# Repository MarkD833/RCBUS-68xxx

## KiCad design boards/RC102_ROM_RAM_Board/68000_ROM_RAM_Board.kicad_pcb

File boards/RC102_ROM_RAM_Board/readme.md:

# ROM & RAM board - V1 - 128K ROM + 1M RAM

# Details
The ROM & RAM board is designed to plug into an RCBus-80 backplane with support for 128K ROM (via 2x Winbond W27C512 EEPROMs) and 1M RAM (via 2x Alliance Memory AS6C4008 SRAMs). The EEPROMs and SRAMs are used as a pair to allow 16-bit wide memory accesses.

## Address Decoding
The address decoding is carried out by a 74LS138 and divides the lower 8Mb of memory space into eight 1Mb blocks. The EEPROMs are hard wired to /CS0 (pin 15) and the SRAMs are hard wired to /CS1 (pin 14). This configuration always places the EEPROMs starting at address 0x000000 and the SRAMs starting at address 0x100000.

## Bus Width 
A 74LS139 generates the read and write signals for each of the memory chips and takes care of byte or word accesses.

## DTACK
A 74LS125 is used to generate a simple /DTACK signal driven directly from the EEPROM and SRAM chip select signals without any wait period.

# Board Assembly
Assembly of the board should be fairly straightforward as there are no surface mount devices to deal with.

When fitting the 80-pin right angle connector, initially only solder a couple of pins at opposite ends of the connector so that you can make any adjustments if the board is not vertical when fitted to the backplane.

# Winbond W27C512 EEPROMs
Be careful where you source these devices from. I bought mine from AliExpress and they were sold as new. In fact they were salvaged from boards and the IC legs were tinned with solder. This makes the pins slightly "sticky" when you insert the chips into IC sockets. My experience with these chips is that you may get 6-10 insertions/removals before the IC socket spring contacts start to break.

# Errors
None so far.

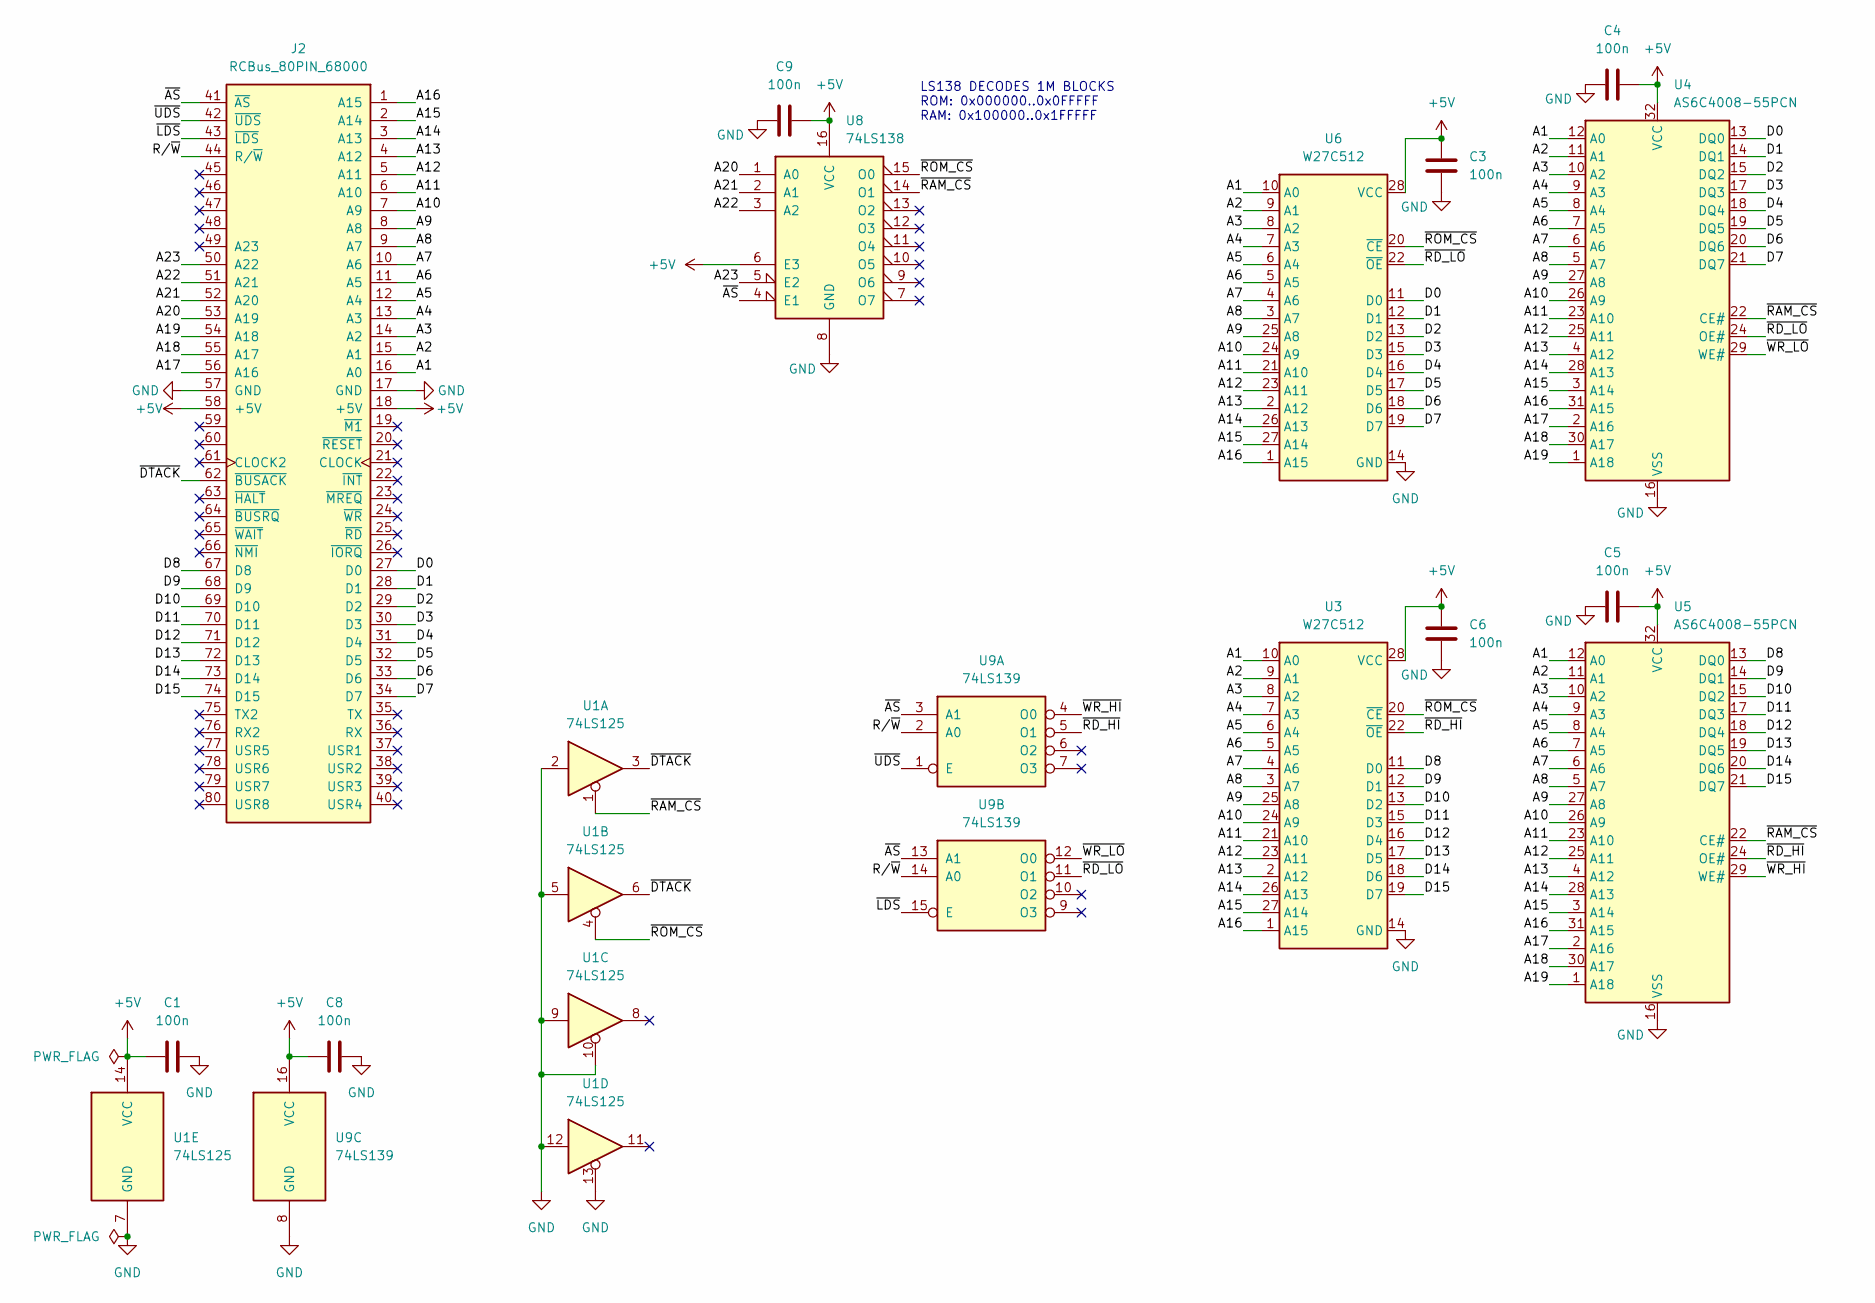
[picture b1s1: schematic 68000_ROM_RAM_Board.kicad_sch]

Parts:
C1, C3, C4, C5, C6, C8, C9: 100n; C_Disc_D5.0mm_W2.5mm_P2.50mm
J2: RCBus_80PIN_68000; RCBus_80p_Medium
U1: 74LS125; DIP-14_W7.62mm
U3, U6: W27C512; DIP-28_W15.24mm
U4, U5: AS6C4008-55PCN; DIP-32_W15.24mm
U8: 74LS138; DIP-16_W7.62mm
U9: 74LS139; DIP-16_W7.62mm

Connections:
+5V: C1.1, C3.1, C4.2, C5.2, C6.1, C8.1, C9.2, J2.18 (+5V), J2.58 (+5V), U1.14 (VCC), U3.28 (VCC), U4.32 (VCC), U5.32 (VCC), U6.28 (VCC), U8.6 (E3), U8.16 (VCC), U9.16 (VCC)
/A1: J2.16 (A0), U3.10 (A0), U4.12 (A0), U5.12 (A0), U6.10 (A0)
/A2: J2.15 (A1), U3.9 (A1), U4.11 (A1), U5.11 (A1), U6.9 (A1)
/A3: J2.14 (A2), U3.8 (A2), U4.10 (A2), U5.10 (A2), U6.8 (A2)
/A4: J2.13 (A3), U3.7 (A3), U4.9 (A3), U5.9 (A3), U6.7 (A3)
/A5: J2.12 (A4), U3.6 (A4), U4.8 (A4), U5.8 (A4), U6.6 (A4)
/A6: J2.11 (A5), U3.5 (A5), U4.7 (A5), U5.7 (A5), U6.5 (A5)
/A7: J2.10 (A6), U3.4 (A6), U4.6 (A6), U5.6 (A6), U6.4 (A6)
/A8: J2.9 (A7), U3.3 (A7), U4.5 (A7), U5.5 (A7), U6.3 (A7)
/A9: J2.8 (A8), U3.25 (A8), U4.27 (A8), U5.27 (A8), U6.25 (A8)
/A10: J2.7 (A9), U3.24 (A9), U4.26 (A9), U5.26 (A9), U6.24 (A9)
/A11: J2.6 (A10), U3.21 (A10), U4.23 (A10), U5.23 (A10), U6.21 (A10)
/A12: J2.5 (A11), U3.23 (A11), U4.25 (A11), U5.25 (A11), U6.23 (A11)
/A13: J2.4 (A12), U3.2 (A12), U4.4 (A12), U5.4 (A12), U6.2 (A12)
/A14: J2.3 (A13), U3.26 (A13), U4.28 (A13), U5.28 (A13), U6.26 (A13)
/A15: J2.2 (A14), U3.27 (A14), U4.3 (A14), U5.3 (A14), U6.27 (A14)
/A16: J2.1 (A15), U3.1 (A15), U4.31 (A15), U5.31 (A15), U6.1 (A15)
/A17: J2.56 (A16), U4.2 (A16), U5.2 (A16)
/A18: J2.55 (A17), U4.30 (A17), U5.30 (A17)
/A19: J2.54 (A18), U4.1 (A18), U5.1 (A18)
/A20: J2.53 (A19), U8.1 (A0)
/A21: J2.52 (A20), U8.2 (A1)
/A22: J2.51 (A21), U8.3 (A2)
/A23: J2.50 (A22), U8.5 (E2)
/D0: J2.27 (D0), U4.13 (DQ0), U6.11 (D0)
/D1: J2.28 (D1), U4.14 (DQ1), U6.12 (D1)
/D2: J2.29 (D2), U4.15 (DQ2), U6.13 (D2)
/D3: J2.30 (D3), U4.17 (DQ3), U6.15 (D3)
/D4: J2.31 (D4), U4.18 (DQ4), U6.16 (D4)
/D5: J2.32 (D5), U4.19 (DQ5), U6.17 (D5)
/D6: J2.33 (D6), U4.20 (DQ6), U6.18 (D6)
/D7: J2.34 (D7), U4.21 (DQ7), U6.19 (D7)
/D8: J2.67 (D8), U3.11 (D0), U5.13 (DQ0)
/D9: J2.68 (D9), U3.12 (D1), U5.14 (DQ1)
/D10: J2.69 (D10), U3.13 (D2), U5.15 (DQ2)
/D11: J2.70 (D11), U3.15 (D3), U5.17 (DQ3)
/D12: J2.71 (D12), U3.16 (D4), U5.18 (DQ4)
/D13: J2.72 (D13), U3.17 (D5), U5.19 (DQ5)
/D14: J2.73 (D14), U3.18 (D6), U5.20 (DQ6)
/D15: J2.74 (D15), U3.19 (D7), U5.21 (DQ7)
/R/~W: J2.44 (R/~W), U9.2 (A0), U9.14 (A0)
/~AS: J2.41 (~AS), U8.4 (E1), U9.3 (A1), U9.13 (A1)
/~DTACK: J2.62 (~BUSACK), U1.3, U1.6
/~LDS: J2.43 (~LDS), U9.15 (E)
/~RAM_CS: U1.1, U4.22 (CE#), U5.22 (CE#), U8.14 (O1)
/~RD_HI: U3.22 (~OE), U5.24 (OE#), U9.5 (O1)
/~RD_LO: U4.24 (OE#), U6.22 (~OE), U9.11 (O1)
/~ROM_CS: U1.4, U3.20 (~CE), U6.20 (~CE), U8.15 (O0)
/~UDS: J2.42 (~UDS), U9.1 (E)
/~WR_HI: U5.29 (WE#), U9.4 (O0)
/~WR_LO: U4.29 (WE#), U9.12 (O0)
GND: C1.2, C3.2, C4.1, C5.1, C6.2, C8.2, C9.1, J2.17 (GND), J2.57 (GND), U1.2, U1.5, U1.7 (GND), U1.9, U1.10, U1.12, U1.13, U3.14 (GND), U4.16 (VSS), U5.16 (VSS), U6.14 (GND), U8.8 (GND), U9.8 (GND)

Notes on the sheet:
LS138 DECODES 1M BLOCKS ROM: 0x000000..0x0FFFFF RAM: 0x100000..0x1FFFFF

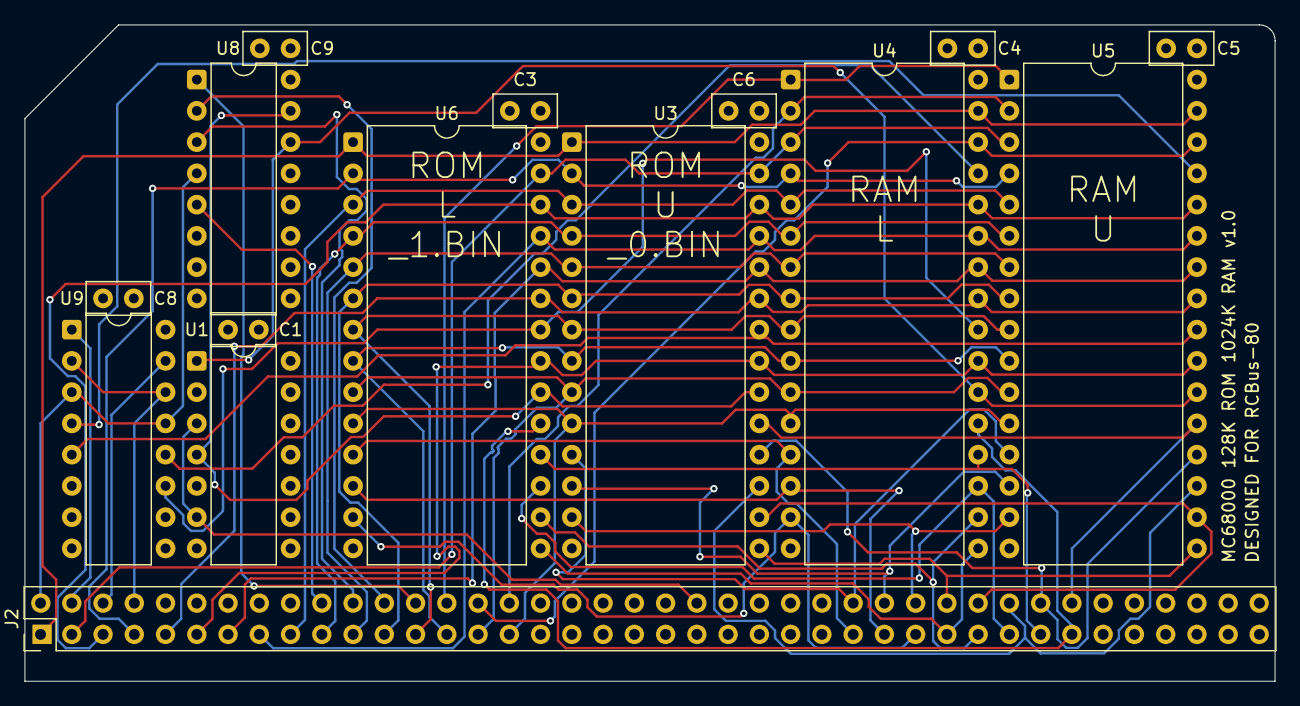
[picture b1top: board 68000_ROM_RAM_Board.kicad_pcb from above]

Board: 4 copper layers, 101.6 x 53.3 mm, 15 parts (0 on the bottom side), 52 nets.

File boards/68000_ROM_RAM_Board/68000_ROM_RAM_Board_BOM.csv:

"Reference","Value","Datasheet","Footprint","Qty","Description"
"C1,C3,C4,C5,C6,C8,C9","100n","~","Capacitor_THT:C_Disc_D5.0mm_W2.5mm_P2.50mm","7","Unpolarized ceramic capacitor"
"J2","RCBus_80PIN_68000","~","MyLibrary2023:RCBus_80p_Medium","1","Generic 02x40 pin connector, right angle"
"U1","74LS125","http://www.ti.com/lit/gpn/sn74LS125","Package_DIP:DIP-14_W7.62mm","1","Quad buffer 3-State outputs"
"U3,U6","W27C512","","Package_DIP:DIP-28_W15.24mm","2","EEPROM 64K x 8 DIP28"
"U4,U5","AS6C4008-55PCN","https://www.alliancememory.com/wp-content/uploads/pdf/AS6C4008.pdf","Package_DIP:DIP-32_W15.24mm","2","512K x 8 Low Power CMOS RAM, DIP-32"
"U8","74LS138","http://www.ti.com/lit/gpn/sn74LS138","Package_DIP:DIP-16_W7.62mm","1","Decoder 3 to 8 active low outputs"
"U9","74LS139","http://www.ti.com/lit/ds/symlink/sn74ls139a.pdf","Package_DIP:DIP-16_W7.62mm","1","Dual Decoder 1 of 4, Active low outputs"

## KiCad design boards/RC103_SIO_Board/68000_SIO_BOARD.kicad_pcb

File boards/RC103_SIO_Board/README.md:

# Quad Serial I/O Board

# Details
The serial board is populated with two 68681 (or equivalent) DUARTS giving 4 UARTs in total. The 4 serial ports are each fed to a 6-pin connector at the board edge. The layout of the 6 pins is compatible with an FTDI USB-TTL Serial interface board. Both DUART chips do not have to be fitted. The board will work with just one chip fitted.

## Address Decoding
The address decoding is carried out by a 74LS688 combined with a 74LS138 to generate 8 separate 2048 byte blocks residing between addresses $D00000 and $D03FFF.

The base address of each DUART is determined by the placement of a jumper between adjacent pins on J1 & J9 (DUART A) and J1 & J11 (DUART B).

## Device Register Access
The registers of the 68681 DUART are 8 bits wide and are accessed on consecutive ODD addresses from the base address set by the address decode logic. Assuming that the /CS0 jumper has been fitted for DUART #1, then the first few registers are accessed on the following addresses:
+ $D00001 : Mode Register A (R/W)
+ $D00003 : Status Register A (R) / Clock Select Register A (W)
+ $D00005 : Command Register A (W)

## DTACK
Each DUART generates its own /DTACK signal internally which is then routed back to the processor via RCBus-80 pin 62.

## Interrupts
The current board design combines the interrupts from both DUARTs into a single /INT signal. This /INT signal can then be assigned to an interrupt level of 1,2,5 or 6 depending on the jumper position on J12.

## Baud Rate Generator Clock
The clock signal for the baud rate generators can be sourced from the on board 3.6864MHz crystal oscillator (X1 in the schematic) or from an external clock source on the RCBus-80 CLOCK2 pin (pin 61) via the jumper J14.

The jumper J14 can also be configured to route the baud rate generator clock to the CLOCK2 pin on the RCBus-80 connector.

## Discrete Outputs
The 8 outputs from each DUART are routed to J4 on the edge of the board. J4 also provides GND and +5V signals. Note that the board **does not have** any protection built in to prevent damage to the DUART if one of these pins is mis-used.

## Discrete Inputs
The 6 inputs to each DUART are routed to J10 on the edge of the board. J10 also provides GND and +5V signals. Note that the board **does not have** any protection built in to prevent damage to the DUART if one of these pins is mis-used.

## Flow Control
Serial hardware flow control can be achieved on each of the 4 serial ports by shorting the appropriate solder jumpers on the rear of the board. This routes the 2 flow control signals for each serial port to an input pin and an output pin on the DUART.

## Power
The complete RCBus system can be powered from the 5V pin of one of the USB-TTL serial connectors by fitting a jumper in place on the appropriate pins of J3 or J6.

Note that there is a current limit of 500mA - imposed by the host system USB hardware - when the system is powered this way. It is relatively easy to exceed this limit once several boards are in use and I recommend that the system be powered from an external 5V supply connected to the RCBus backplane instead.
 
# Board Assembly
Assembly of the board should be fairly straightforward. There are no surface mount devices to deal with.

If you choose have a turned pin socket for the system clock, then an 8-pin DIL turned pin socket can be used. I flipped the socket over - pins pointing upwards - and easily pushed out pins 2,3,6 & 7.

A **note of caution** when using a socketed oscillator - there is the possibility that the metal can of the oscillator could accidentally short out pins on the next board. Please be aware of this.

When fitting the 80-pin right angle connector, initially only solder a couple of pins at opposite ends of the connector so that you can make any adjustments if the board is not vertical when fitted to the backplane.

# Choice of DUART Chip
There are various 68681 DUARTs but unfortunately they are not all entirely compatible. The issue appears to be in relation to the X2 input pin when an external oscillator is used rather than a crystal, specifically whether the X2 pin should be grounded or not. My current SIO board design grounds the X2 pin which limits the DUART choices to those devices that allow the X2 pin to be grounded. However you may be able to work around this by bending the X2 pin up so that it does not go into the IC socket.

Below are some 68681 DUARTs from different manufacturers and the relevant text from their datasheets:

+ Motorola MC68681 (max 38400 baud)
  + If an external TTL-level clock is used, this pin should be tied to ground. 
+ Motorola MC68HC681 (max 38400 baud)
  +  If an external CMOS-level clock is used, this pin must be left open. 
+ Philips SCC68681 (max 115200 baud)
  + If a crystal is not used it is best to keep this pin not connected. It **must not** be grounded.
+ Philips SCN68681 (max 115200 baud)
  + If a crystal is not used it is best to keep this pin not connected although it is permissible to ground it.
+ Philips SCC68692 (max 115200 baud)
  + If a crystal is not used it is best to keep this pin not connected although it is permissible to ground it.
+ Toshiba TMP68681 (max 38400 baud)
  + If an external TTL-level clock is used, this pin should be tied to ground. 

For the Philips devices that support 115200 baud, this is achieved by putting the device into a test mode and is documented in the Philips Semiconductors document titled "Extended baud rates for SCN2681, SCN68681, SCC2691, SCC2692, SCC68681 and SCC2698B".

# Jumpers
+ J1: IO Address selection
  + $D00000
  + $D00800
  + $D01000
  + $D01800
  + $D02000
  + $D02800
  + $D03000
  + $D03800
+ J2: Serial #3 port
+ J3: (**only fit one jumper** if not using an external 5V power source)
  + 1-2 : Power the system from the USB-TTL Serial board on Serial #1
  + 2-3 : Power the system from the USB-TTL Serial board on Serial #2
  + 1-2 : Power the system from the USB-TTL Serial board on Serial #3
  + 2-3 : Power the system from the USB-TTL Serial board on Serial #4
+ J4: Exposes the 16 digital outputs from the 2 DUARTS as well as GND and +5V. Note that there is **NO** output protection circuitry.
+ J5: Serial #4 port
+ J7: Serial #1 port
+ J8: Serial #2 port
+ J9 (with J1): Specify the IO Address for Serial chip A
+ J10: Exposes the 12 digital inputs to the 2 DUARTS as well as GND and +5V. Note that there is **NO** input protection circuitry.
+ J11 (with J1): Specify the IO Address for Serial chip B
+ J12: Specify the interupt line to be used by the serial cards
  + 1-2 : use /INT1
  + 3-4 : use /INT2
  + 5-6 : use /INT5
  + 7-8 : use /INT6 
+ J14: Specifies the clock source for the DUART baud rate generators
  + 1-3 Use the onboard clock source
  + 1-2 Use the RCBus clock source from CLOCK2
  + 1-2 *and* 3-4: Use the onboard clock source and supply the RCBus CLOCK2 signal with the clock.

# Errors
None so far.

# Thoughts / Enhancements
+ Should the SIOs each have their own choice of interrupt level?
+ Move the 6-pin serial port connectors further in from the board edge.
+ Jumpers to allow TXD1 & RXD1 to route to the RCBus TX & RX signals.
+ Jumpers to allow TXD2 & RXD2 to route to the RCBus TX2 & RX2 signals.
+ Board would support a wider range of compatible 68681s with a solder jumper between the X2 pin and GND.

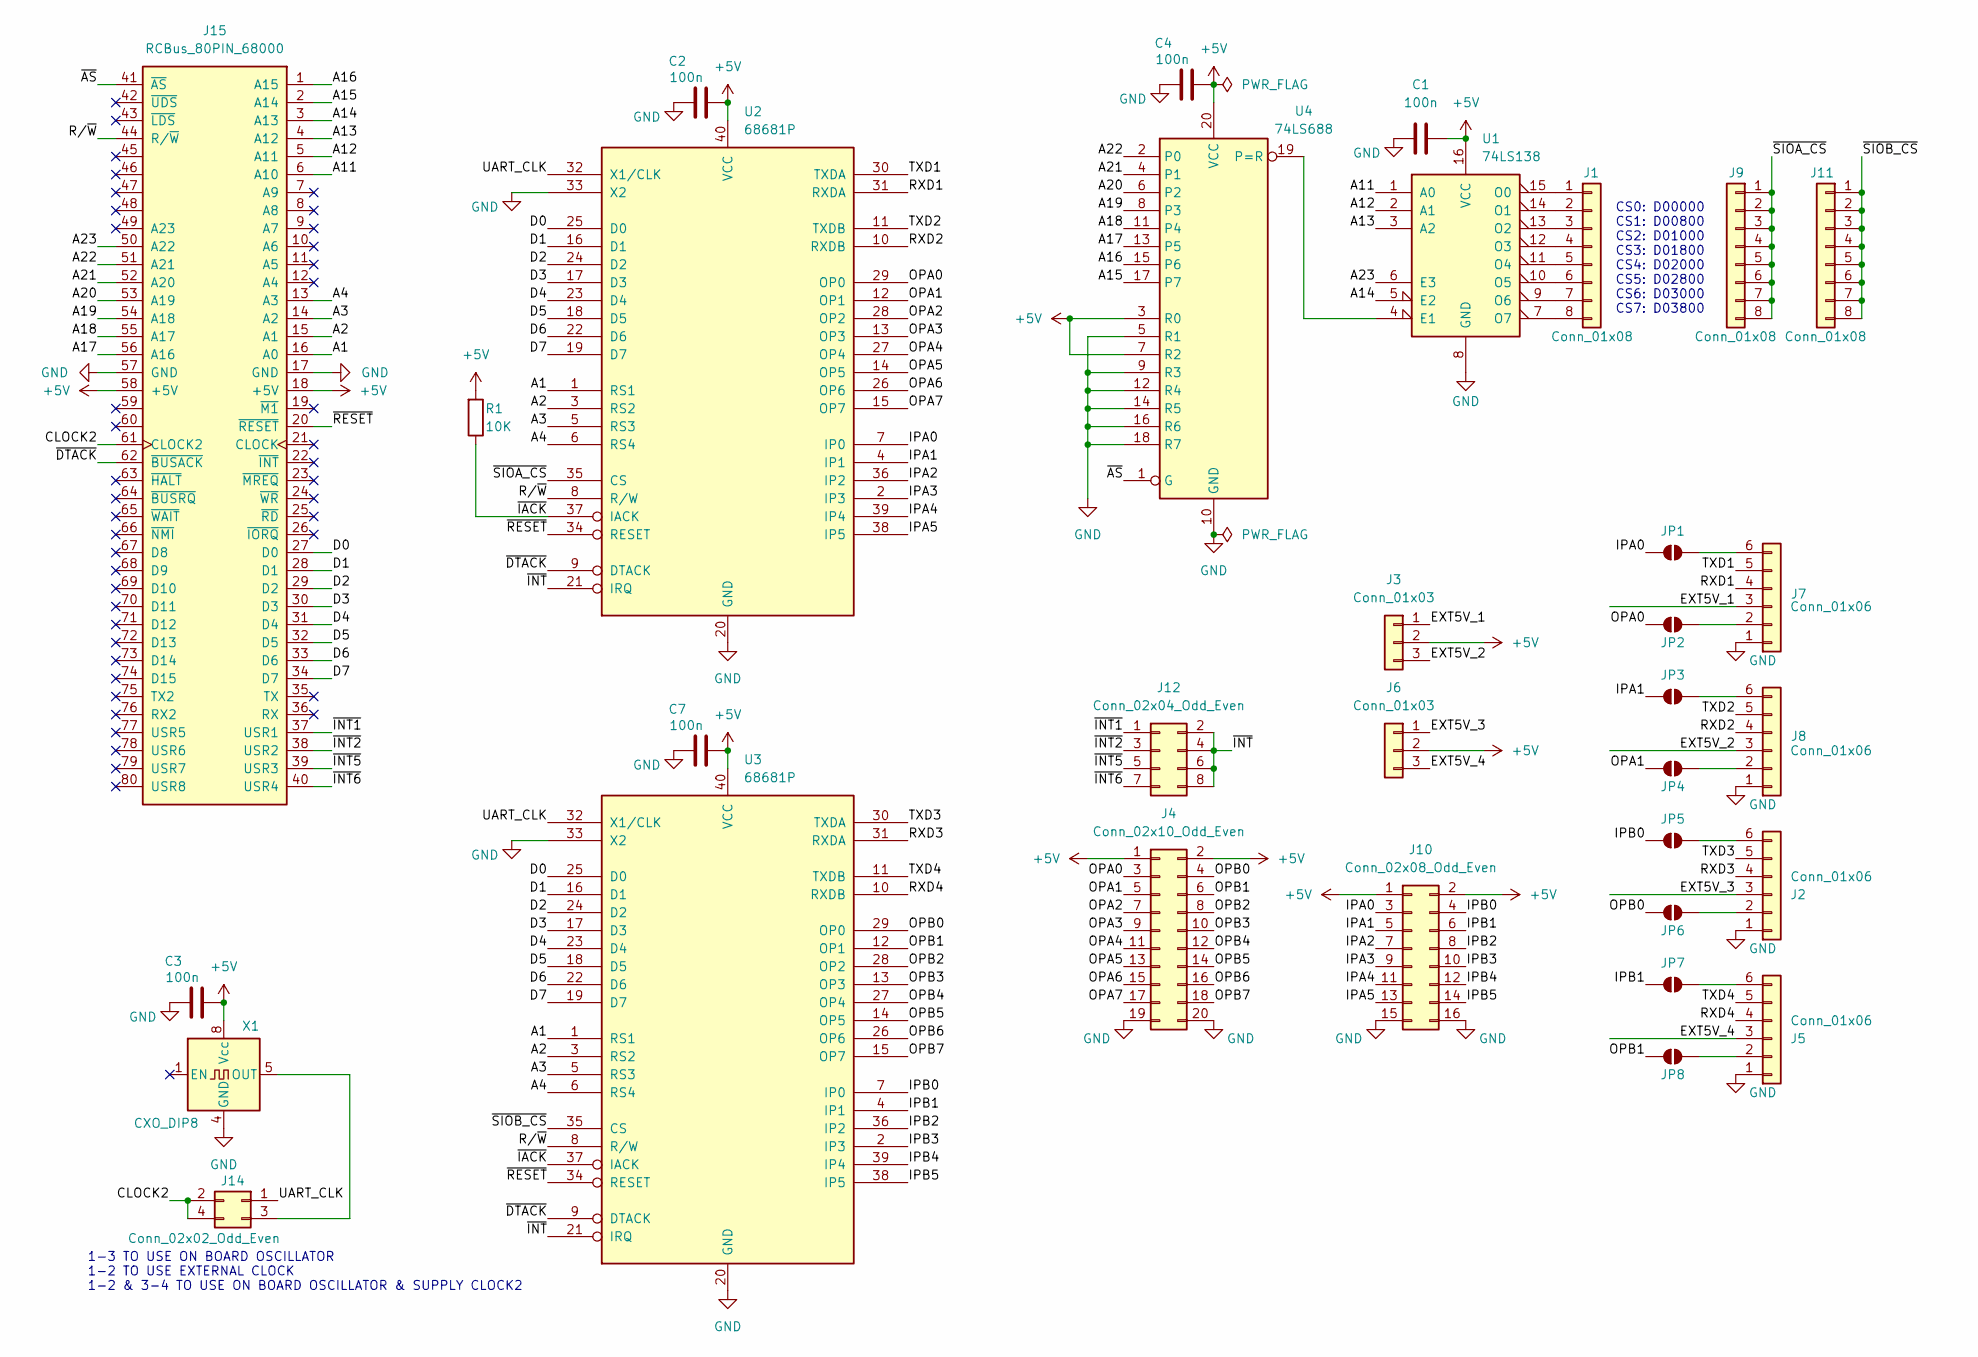
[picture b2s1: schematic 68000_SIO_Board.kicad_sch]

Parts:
C1, C2, C3, C4, C7: 100n; C_Disc_D5.0mm_W2.5mm_P2.50mm
J1, J9, J11: Conn_01x08; PinHeader_1x08_P2.54mm_Vertical
J2, J5, J7, J8: Conn_01x06; PinSocket_1x06_P2.54mm_Horizontal
J3, J6: Conn_01x03; PinHeader_1x03_P2.54mm_Vertical
J4: Conn_02x10_Odd_Even; PinHeader_2x10_P2.54mm_Horizontal
J10: Conn_02x08_Odd_Even; PinHeader_2x08_P2.54mm_Horizontal
J12: Conn_02x04_Odd_Even; PinHeader_2x04_P2.54mm_Vertical
J14: Conn_02x02_Odd_Even; PinHeader_2x02_P2.54mm_Vertical
J15: RCBus_80PIN_68000; RCBus_80p_Medium
JP1, JP2, JP3, JP4, JP5, JP6, JP7, JP8: SolderJumper; SolderJumper-2_P1.3mm_Open_Pad1.0x1.5mm
R1: 10K; R_Axial_DIN0207_L6.3mm_D2.5mm_P7.62mm_Horizontal
U1: 74LS138; DIP-16_W7.62mm_Socket
U2, U3: 68681P; DIP-40_W15.24mm_Socket
U4: 74LS688; DIP-20_W7.62mm_Socket
X1: CXO_DIP8; Oscillator_DIP-8

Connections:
+5V: C1.2, C2.2, C3.2, C4.2, C7.2, J3.2, J4.1, J4.2, J6.2, J10.1, J10.2, J15.18 (+5V), J15.58 (+5V), R1.2, U1.16 (VCC), U2.40 (VCC), U3.40 (VCC), U4.3 (R0), U4.7 (R2), U4.20 (VCC), X1.8 (Vcc)
/A1: J15.16 (A0), U2.1 (RS1), U3.1 (RS1)
/A2: J15.15 (A1), U2.3 (RS2), U3.3 (RS2)
/A3: J15.14 (A2), U2.5 (RS3), U3.5 (RS3)
/A4: J15.13 (A3), U2.6 (RS4), U3.6 (RS4)
/A11: J15.6 (A10), U1.1 (A0)
/A12: J15.5 (A11), U1.2 (A1)
/A13: J15.4 (A12), U1.3 (A2)
/A14: J15.3 (A13), U1.5 (E2)
/A15: J15.2 (A14), U4.17 (P7)
/A16: J15.1 (A15), U4.15 (P6)
/A17: J15.56 (A16), U4.13 (P5)
/A18: J15.55 (A17), U4.11 (P4)
/A19: J15.54 (A18), U4.8 (P3)
/A20: J15.53 (A19), U4.6 (P2)
/A21: J15.52 (A20), U4.4 (P1)
/A22: J15.51 (A21), U4.2 (P0)
/A23: J15.50 (A22), U1.6 (E3)
/CLOCK2: J14.2, J14.4, J15.61 (CLOCK2)
/D0: J15.27 (D0), U2.25 (D0), U3.25 (D0)
/D1: J15.28 (D1), U2.16 (D1), U3.16 (D1)
/D2: J15.29 (D2), U2.24 (D2), U3.24 (D2)
/D3: J15.30 (D3), U2.17 (D3), U3.17 (D3)
/D4: J15.31 (D4), U2.23 (D4), U3.23 (D4)
/D5: J15.32 (D5), U2.18 (D5), U3.18 (D5)
/D6: J15.33 (D6), U2.22 (D6), U3.22 (D6)
/D7: J15.34 (D7), U2.19 (D7), U3.19 (D7)
/EXT5V_1: J3.1, J7.3
/EXT5V_2: J3.3, J8.3
/EXT5V_3: J2.3, J6.1
/EXT5V_4: J5.3, J6.3
/IPA0: J10.3, JP1.1 (A), U2.7 (IP0)
/IPA1: J10.5, JP3.1 (A), U2.4 (IP1)
/IPA2: J10.7, U2.36 (IP2)
/IPA3: J10.9, U2.2 (IP3)
/IPA4: J10.11, U2.39 (IP4)
/IPA5: J10.13, U2.38 (IP5)
/IPB0: J10.4, JP5.1 (A), U3.7 (IP0)
/IPB1: J10.6, JP7.1 (A), U3.4 (IP1)
/IPB2: J10.8, U3.36 (IP2)
/IPB3: J10.10, U3.2 (IP3)
/IPB4: J10.12, U3.39 (IP4)
/IPB5: J10.14, U3.38 (IP5)
/OPA0: J4.3, JP2.1 (A), U2.29 (OP0)
/OPA1: J4.5, JP4.1 (A), U2.12 (OP1)
/OPA2: J4.7, U2.28 (OP2)
/OPA3: J4.9, U2.13 (OP3)
/OPA4: J4.11, U2.27 (OP4)
/OPA5: J4.13, U2.14 (OP5)
/OPA6: J4.15, U2.26 (OP6)
/OPA7: J4.17, U2.15 (OP7)
/OPB0: J4.4, JP6.1 (A), U3.29 (OP0)
/OPB1: J4.6, JP8.1 (A), U3.12 (OP1)
/OPB2: J4.8, U3.28 (OP2)
/OPB3: J4.10, U3.13 (OP3)
/OPB4: J4.12, U3.27 (OP4)
/OPB5: J4.14, U3.14 (OP5)
/OPB6: J4.16, U3.26 (OP6)
/OPB7: J4.18, U3.15 (OP7)
/RXD1: J7.4, U2.31 (RXDA)
/RXD2: J8.4, U2.10 (RXDB)
/RXD3: J2.4, U3.31 (RXDA)
/RXD4: J5.4, U3.10 (RXDB)
/R/~W: J15.44 (R/~W), U2.8 (R/W), U3.8 (R/W)
/TXD1: J7.5, U2.30 (TXDA)
/TXD2: J8.5, U2.11 (TXDB)
/TXD3: J2.5, U3.30 (TXDA)
/TXD4: J5.5, U3.11 (TXDB)
/UART_CLK: J14.1, U2.32 (X1/CLK), U3.32 (X1/CLK)
/~AS: J15.41 (~AS), U4.1 (G)
/~DTACK: J15.62 (~BUSACK), U2.9 (DTACK), U3.9 (DTACK)
/~IACK: R1.1, U2.37 (IACK), U3.37 (IACK)
/~INT1: J12.1, J15.37 (USR1)
/~INT2: J12.3, J15.38 (USR2)
/~INT5: J12.5, J15.39 (USR3)
/~INT6: J12.7, J15.40 (USR4)
/~INT: J12.2, J12.4, J12.6, J12.8, U2.21 (IRQ), U3.21 (IRQ)
/~RESET: J15.20 (~RESET), U2.34 (RESET), U3.34 (RESET)
/~SIOA_CS: J9.1, J9.2, J9.3, J9.4, J9.5, J9.6, J9.7, J9.8, U2.35 (CS)
/~SIOB_CS: J11.1, J11.2, J11.3, J11.4, J11.5, J11.6, J11.7, J11.8, U3.35 (CS)
GND: C1.1, C2.1, C3.1, C4.1, C7.1, J2.1, J4.19, J4.20, J5.1, J7.1, J8.1, J10.15, J10.16, J15.17 (GND), J15.57 (GND), U1.8 (GND), U2.20 (GND), U2.33 (X2), U3.20 (GND), U3.33 (X2), U4.5 (R1), U4.9 (R3), U4.10 (GND), U4.12 (R4), U4.14 (R5), U4.16 (R6), U4.18 (R7), X1.4 (GND)
unnamed: J1.1, U1.15 (O0)
unnamed: J1.2, U1.14 (O1)
unnamed: J1.3, U1.13 (O2)
unnamed: J1.4, U1.12 (O3)
unnamed: J1.5, U1.11 (O4)
unnamed: J1.6, U1.10 (O5)
unnamed: J1.7, U1.9 (O6)
unnamed: J1.8, U1.7 (O7)
unnamed: J2.2, JP6.2 (B)
unnamed: J2.6, JP5.2 (B)
unnamed: J5.2, JP8.2 (B)
unnamed: J5.6, JP7.2 (B)
unnamed: J7.2, JP2.2 (B)
unnamed: J7.6, JP1.2 (B)
unnamed: J8.2, JP4.2 (B)
unnamed: J8.6, JP3.2 (B)
unnamed: J14.3, X1.5 (OUT)
unnamed: U1.4 (E1), U4.19 (P=R)

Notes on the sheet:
CS0: D00000 CS1: D00800 CS2: D01000 CS3: D01800 CS4: D02000 CS5: D02800 CS6: D03000 CS7: D03800
1-3 TO USE ON BOARD OSCILLATOR 1-2 TO USE EXTERNAL CLOCK 1-2 & 3-4 TO USE ON BOARD OSCILLATOR & SUPPLY CLOCK2

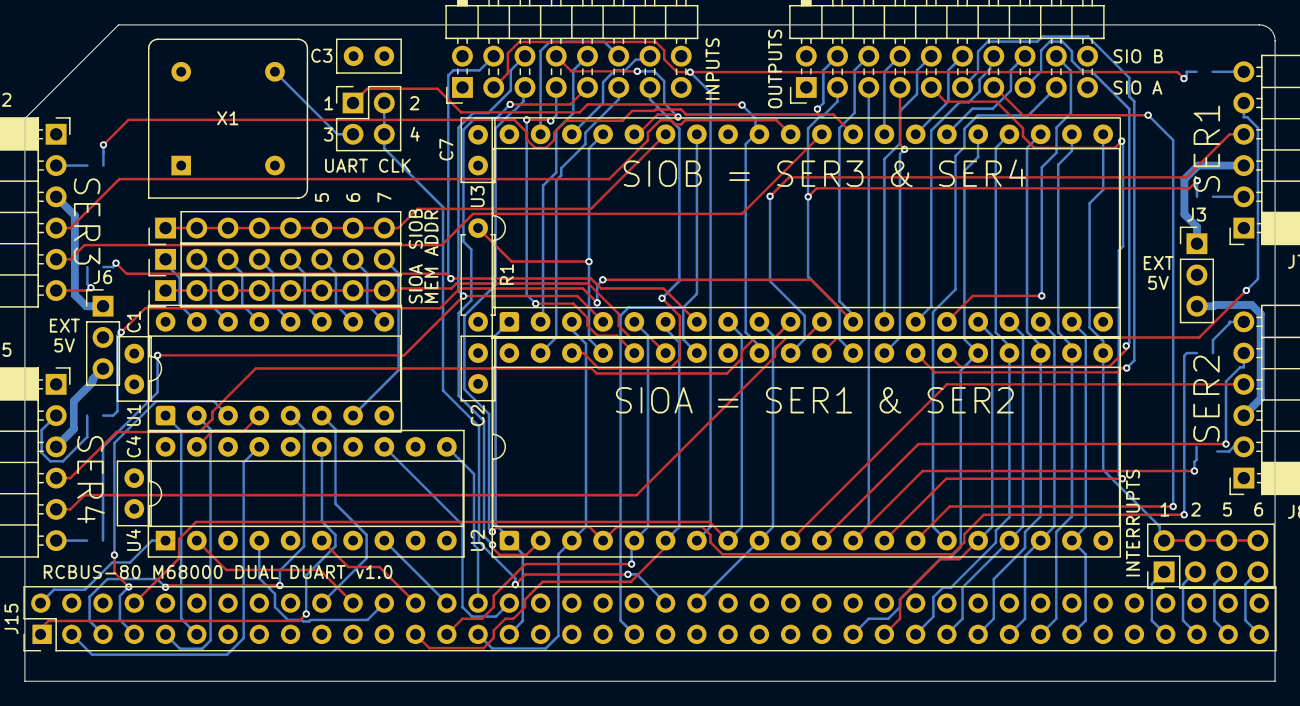
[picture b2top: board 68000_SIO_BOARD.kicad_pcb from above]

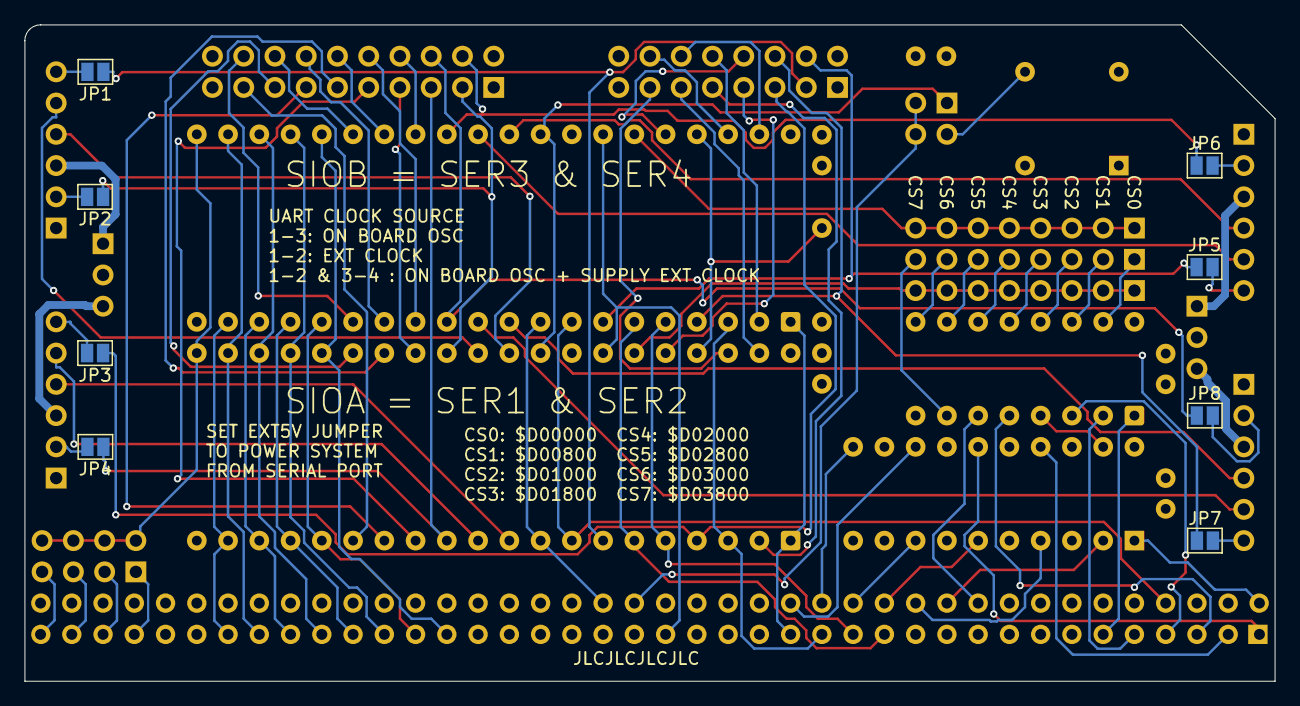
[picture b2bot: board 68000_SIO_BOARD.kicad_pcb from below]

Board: 4 copper layers, 101.6 x 53.3 mm, 33 parts (8 on the bottom side), 99 nets.

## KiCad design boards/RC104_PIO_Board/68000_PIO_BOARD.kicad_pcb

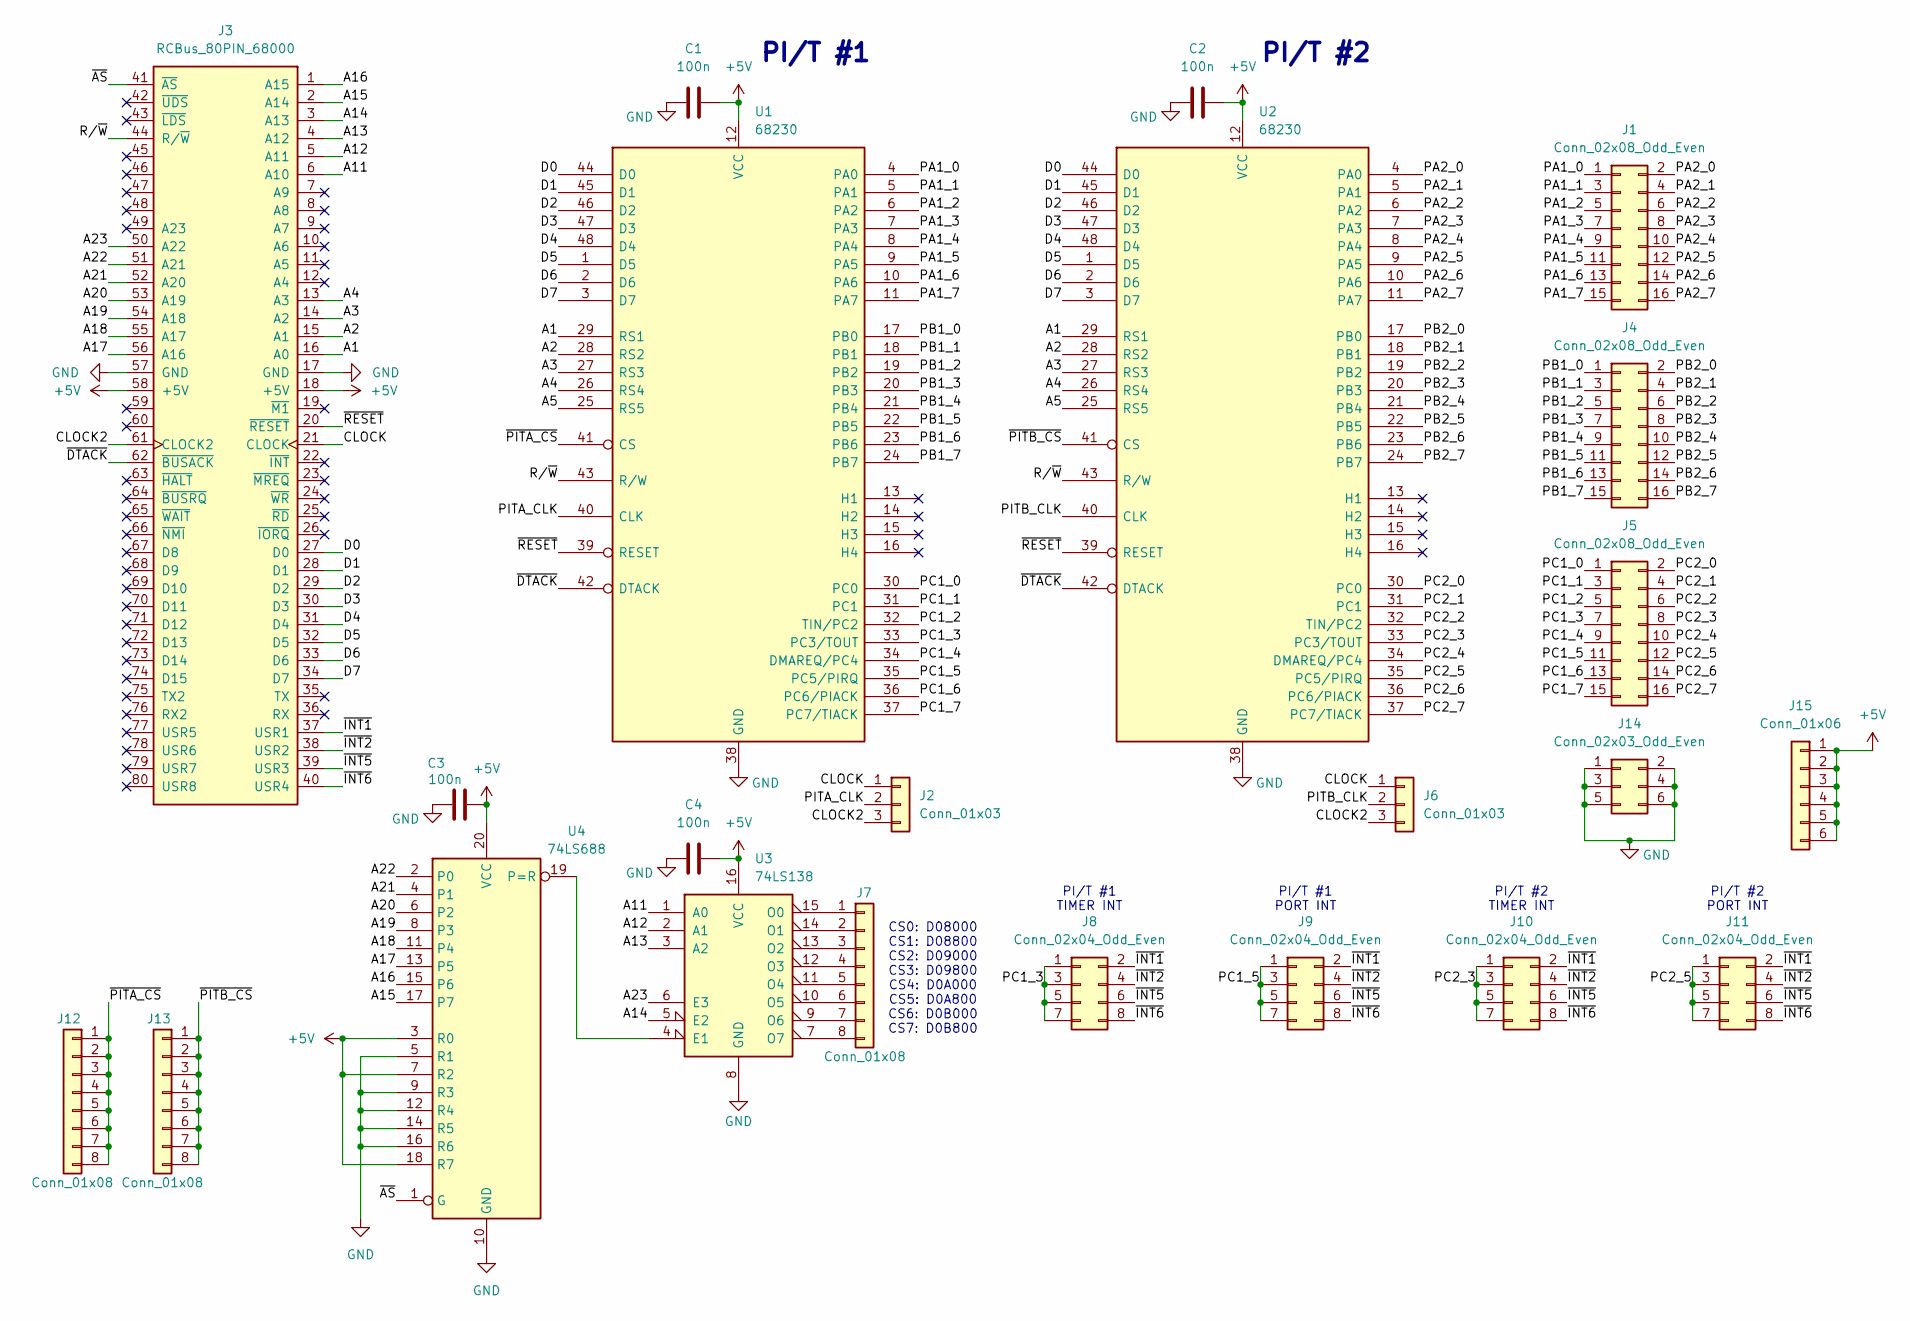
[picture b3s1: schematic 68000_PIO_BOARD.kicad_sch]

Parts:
C1, C2, C3, C4: 100n; C_Disc_D5.0mm_W2.5mm_P2.50mm
J1, J4, J5: Conn_02x08_Odd_Even; PinHeader_2x08_P2.54mm_Vertical
J2, J6: Conn_01x03; PinHeader_1x03_P2.54mm_Vertical
J3: RCBus_80PIN_68000; RCBus_80p_Medium
J7, J12, J13: Conn_01x08; PinHeader_1x08_P2.54mm_Vertical
J8, J9, J10, J11: Conn_02x04_Odd_Even; PinHeader_2x04_P2.54mm_Vertical
J14: Conn_02x03_Odd_Even; PinSocket_2x03_P2.54mm_Vertical
J15: Conn_01x06; PinSocket_1x06_P2.54mm_Vertical
U1, U2: 68230; DIP-48_W15.24mm_Socket
U3: 74LS138; DIP-16_W7.62mm_Socket
U4: 74LS688; DIP-20_W7.62mm_Socket

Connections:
+5V: C1.1, C2.1, C3.2, C4.2, J3.18 (+5V), J3.58 (+5V), J15.1, J15.2, J15.3, J15.4, J15.5, J15.6, U1.12 (VCC), U2.12 (VCC), U3.16 (VCC), U4.3 (R0), U4.7 (R2), U4.18 (R7), U4.20 (VCC)
/A1: J3.16 (A0), U1.29 (RS1), U2.29 (RS1)
/A2: J3.15 (A1), U1.28 (RS2), U2.28 (RS2)
/A3: J3.14 (A2), U1.27 (RS3), U2.27 (RS3)
/A4: J3.13 (A3), U1.26 (RS4), U2.26 (RS4)
/A5: U1.25 (RS5), U2.25 (RS5)
/A11: J3.6 (A10), U3.1 (A0)
/A12: J3.5 (A11), U3.2 (A1)
/A13: J3.4 (A12), U3.3 (A2)
/A14: J3.3 (A13), U3.5 (E2)
/A15: J3.2 (A14), U4.17 (P7)
/A16: J3.1 (A15), U4.15 (P6)
/A17: J3.56 (A16), U4.13 (P5)
/A18: J3.55 (A17), U4.11 (P4)
/A19: J3.54 (A18), U4.8 (P3)
/A20: J3.53 (A19), U4.6 (P2)
/A21: J3.52 (A20), U4.4 (P1)
/A22: J3.51 (A21), U4.2 (P0)
/A23: J3.50 (A22), U3.6 (E3)
/CLOCK: J2.1, J3.21 (CLOCK), J6.1
/CLOCK2: J2.3, J3.61 (CLOCK2), J6.3
/D0: J3.27 (D0), U1.44 (D0), U2.44 (D0)
/D1: J3.28 (D1), U1.45 (D1), U2.45 (D1)
/D2: J3.29 (D2), U1.46 (D2), U2.46 (D2)
/D3: J3.30 (D3), U1.47 (D3), U2.47 (D3)
/D4: J3.31 (D4), U1.48 (D4), U2.48 (D4)
/D5: J3.32 (D5), U1.1 (D5), U2.1 (D5)
/D6: J3.33 (D6), U1.2 (D6), U2.2 (D6)
/D7: J3.34 (D7), U1.3 (D7), U2.3 (D7)
/PA1_0: J1.1, U1.4 (PA0)
/PA1_1: J1.3, U1.5 (PA1)
/PA1_2: J1.5, U1.6 (PA2)
/PA1_3: J1.7, U1.7 (PA3)
/PA1_4: J1.9, U1.8 (PA4)
/PA1_5: J1.11, U1.9 (PA5)
/PA1_6: J1.13, U1.10 (PA6)
/PA1_7: J1.15, U1.11 (PA7)
/PA2_0: J1.2, U2.4 (PA0)
/PA2_1: J1.4, U2.5 (PA1)
/PA2_2: J1.6, U2.6 (PA2)
/PA2_3: J1.8, U2.7 (PA3)
/PA2_4: J1.10, U2.8 (PA4)
/PA2_5: J1.12, U2.9 (PA5)
/PA2_6: J1.14, U2.10 (PA6)
/PA2_7: J1.16, U2.11 (PA7)
/PB1_0: J4.1, U1.17 (PB0)
/PB1_1: J4.3, U1.18 (PB1)
/PB1_2: J4.5, U1.19 (PB2)
/PB1_3: J4.7, U1.20 (PB3)
/PB1_4: J4.9, U1.21 (PB4)
/PB1_5: J4.11, U1.22 (PB5)
/PB1_6: J4.13, U1.23 (PB6)
/PB1_7: J4.15, U1.24 (PB7)
/PB2_0: J4.2, U2.17 (PB0)
/PB2_1: J4.4, U2.18 (PB1)
/PB2_2: J4.6, U2.19 (PB2)
/PB2_3: J4.8, U2.20 (PB3)
/PB2_4: J4.10, U2.21 (PB4)
/PB2_5: J4.12, U2.22 (PB5)
/PB2_6: J4.14, U2.23 (PB6)
/PB2_7: J4.16, U2.24 (PB7)
/PC1_0: J5.1, U1.30 (PC0)
/PC1_1: J5.3, U1.31 (PC1)
/PC1_2: J5.5, U1.32 (TIN/PC2)
/PC1_3: J5.7, J8.1, J8.3, J8.5, J8.7, U1.33 (PC3/TOUT)
/PC1_4: J5.9, U1.34 (DMAREQ/PC4)
/PC1_5: J5.11, J9.1, J9.3, J9.5, J9.7, U1.35 (PC5/PIRQ)
/PC1_6: J5.13, U1.36 (PC6/PIACK)
/PC1_7: J5.15, U1.37 (PC7/TIACK)
/PC2_0: J5.2, U2.30 (PC0)
/PC2_1: J5.4, U2.31 (PC1)
/PC2_2: J5.6, U2.32 (TIN/PC2)
/PC2_3: J5.8, J10.1, J10.3, J10.5, J10.7, U2.33 (PC3/TOUT)
/PC2_4: J5.10, U2.34 (DMAREQ/PC4)
/PC2_5: J5.12, J11.1, J11.3, J11.5, J11.7, U2.35 (PC5/PIRQ)
/PC2_6: J5.14, U2.36 (PC6/PIACK)
/PC2_7: J5.16, U2.37 (PC7/TIACK)
/PITA_CLK: J2.2, U1.40 (CLK)
/PITB_CLK: J6.2, U2.40 (CLK)
/R/~W: J3.44 (R/~W), U1.43 (R/W), U2.43 (R/W)
/~AS: J3.41 (~AS), U4.1 (G)
/~DTACK: J3.62 (~BUSACK), U1.42 (DTACK), U2.42 (DTACK)
/~INT1: J3.37 (USR1), J8.2, J9.2, J10.2, J11.2
/~INT2: J3.38 (USR2), J8.4, J9.4, J10.4, J11.4
/~INT5: J3.39 (USR3), J8.6, J9.6, J10.6, J11.6
/~INT6: J3.40 (USR4), J8.8, J9.8, J10.8, J11.8
/~PITA_CS: J12.1, J12.2, J12.3, J12.4, J12.5, J12.6, J12.7, J12.8, U1.41 (CS)
/~PITB_CS: J13.1, J13.2, J13.3, J13.4, J13.5, J13.6, J13.7, J13.8, U2.41 (CS)
/~RESET: J3.20 (~RESET), U1.39 (RESET), U2.39 (RESET)
GND: C1.2, C2.2, C3.1, C4.1, J3.17 (GND), J3.57 (GND), J14.1, J14.2, J14.3, J14.4, J14.5, J14.6, U1.38 (GND), U2.38 (GND), U3.8 (GND), U4.5 (R1), U4.9 (R3), U4.10 (GND), U4.12 (R4), U4.14 (R5), U4.16 (R6)
unnamed: J7.1, U3.15 (O0)
unnamed: J7.2, U3.14 (O1)
unnamed: J7.3, U3.13 (O2)
unnamed: J7.4, U3.12 (O3)
unnamed: J7.5, U3.11 (O4)
unnamed: J7.6, U3.10 (O5)
unnamed: J7.7, U3.9 (O6)
unnamed: J7.8, U3.7 (O7)
unnamed: U3.4 (E1), U4.19 (P=R)

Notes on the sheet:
PI/T #2 PORT INT
PI/T #1 PORT INT
PI/T #2
CS0: D08000 CS1: D08800 CS2: D09000 CS3: D09800 CS4: D0A000 CS5: D0A800 CS6: D0B000 CS7: D0B800
PI/T #1 TIMER INT
PI/T #2 TIMER INT
PI/T #1
